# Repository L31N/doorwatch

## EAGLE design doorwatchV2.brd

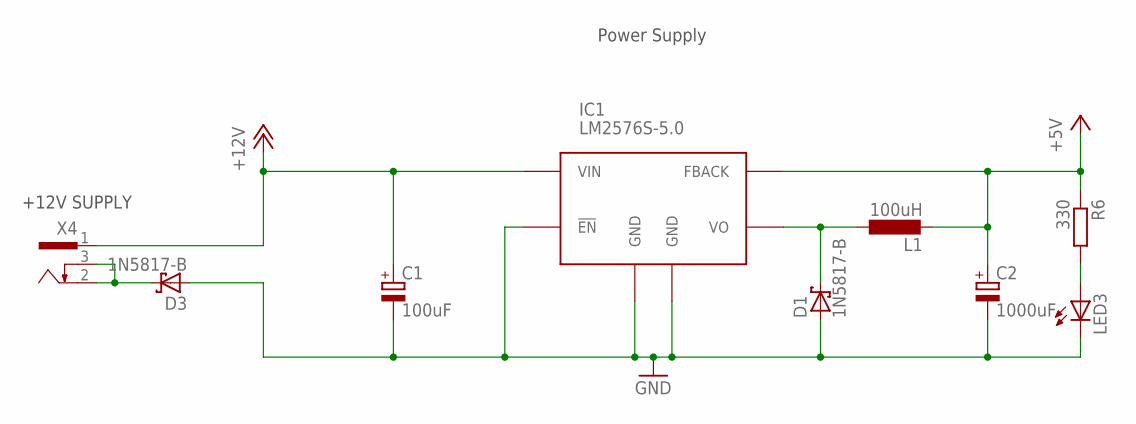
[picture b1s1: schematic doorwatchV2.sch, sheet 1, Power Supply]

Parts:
C1: 100uF; E2,5-7
C2: 1000uF; E5-10,5
D1, D3: 1N5817-B; DO41-7.6
IC1: LM2576S-5.0; TO263-5
L1: 100uH; 2200-20.32
LED3: LEDCHIP-LED0805; CHIP-LED0805
R6: 330; M0805
X4: 733980-62

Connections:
+5V: C2.+, IC1.4 (FBACK), L1.2, R6.1; also elsewhere on the board
+12V: C1.+, IC1.1 (VIN), X4.1; also elsewhere on the board
GND: C1.-, C2.-, D1.A, D3.A, IC1.3 (GND), IC1.5 (!EN), IC1.TAB (GND), LED3.C; also elsewhere on the board
unnamed: D1.C, IC1.2 (VO), L1.1
unnamed: D3.C, X4.2, X4.3
unnamed: LED3.A, R6.2

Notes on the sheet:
+12V SUPPLY
Power Supply

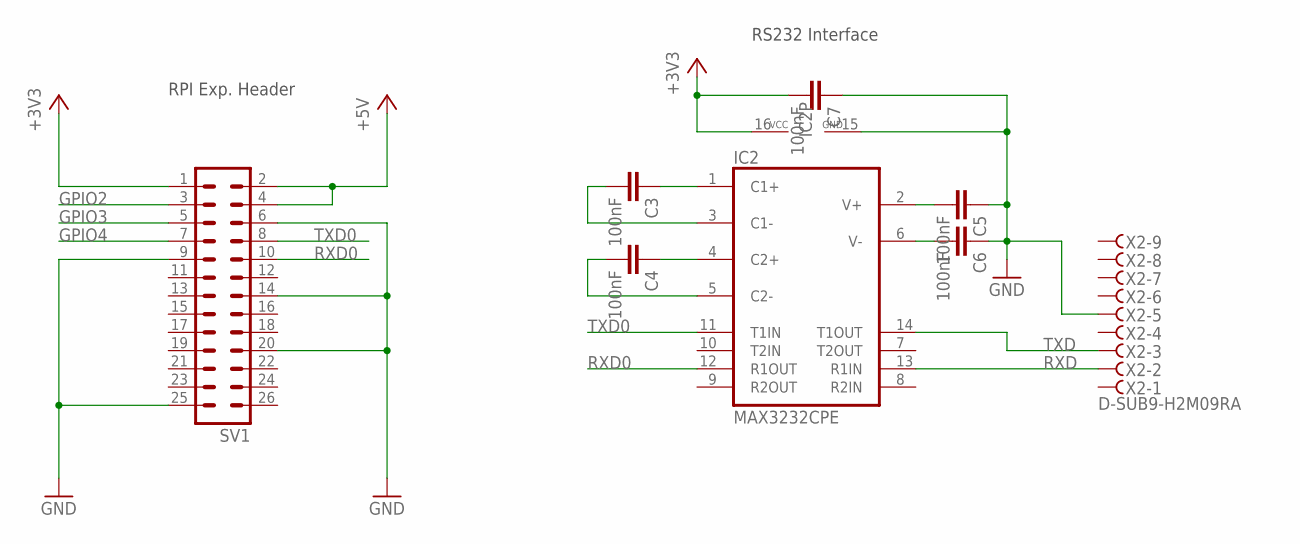
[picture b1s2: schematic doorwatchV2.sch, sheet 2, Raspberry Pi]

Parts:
C3, C4, C5, C6, C7: 100nF; C0805
IC2: MAX3232CPE; DIL16
SV1: ML26
X2: D-SUB9-H2M09RA; H2M09RA

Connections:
+3V3: C7.2, IC2.16 (VCC), SV1.1
+5V: SV1.2, SV1.4; also elsewhere on the board
GND: C5.1, C6.1, C7.1, IC2.15 (GND), SV1.6, SV1.9, SV1.14, SV1.20, SV1.25, X2.5; also elsewhere on the board
GPIO2: SV1.3; also elsewhere on the board
GPIO3: SV1.5; also elsewhere on the board
GPIO4: SV1.7; also elsewhere on the board
unnamed: C3.1, IC2.1 (C1+)
unnamed: C4.1, IC2.4 (C2+)
unnamed: C3.2, IC2.3 (C1-)
unnamed: C4.2, IC2.5 (C2-)
unnamed: C6.2, IC2.6 (V-)
unnamed: C5.2, IC2.2 (V+)
RXD: IC2.13 (R1IN), X2.2
RXD0: IC2.12 (R1OUT), SV1.10
TXD: IC2.14 (T1OUT), X2.3
TXD0: IC2.11 (T1IN), SV1.8

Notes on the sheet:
RPI Exp. Header
RS232 Interface

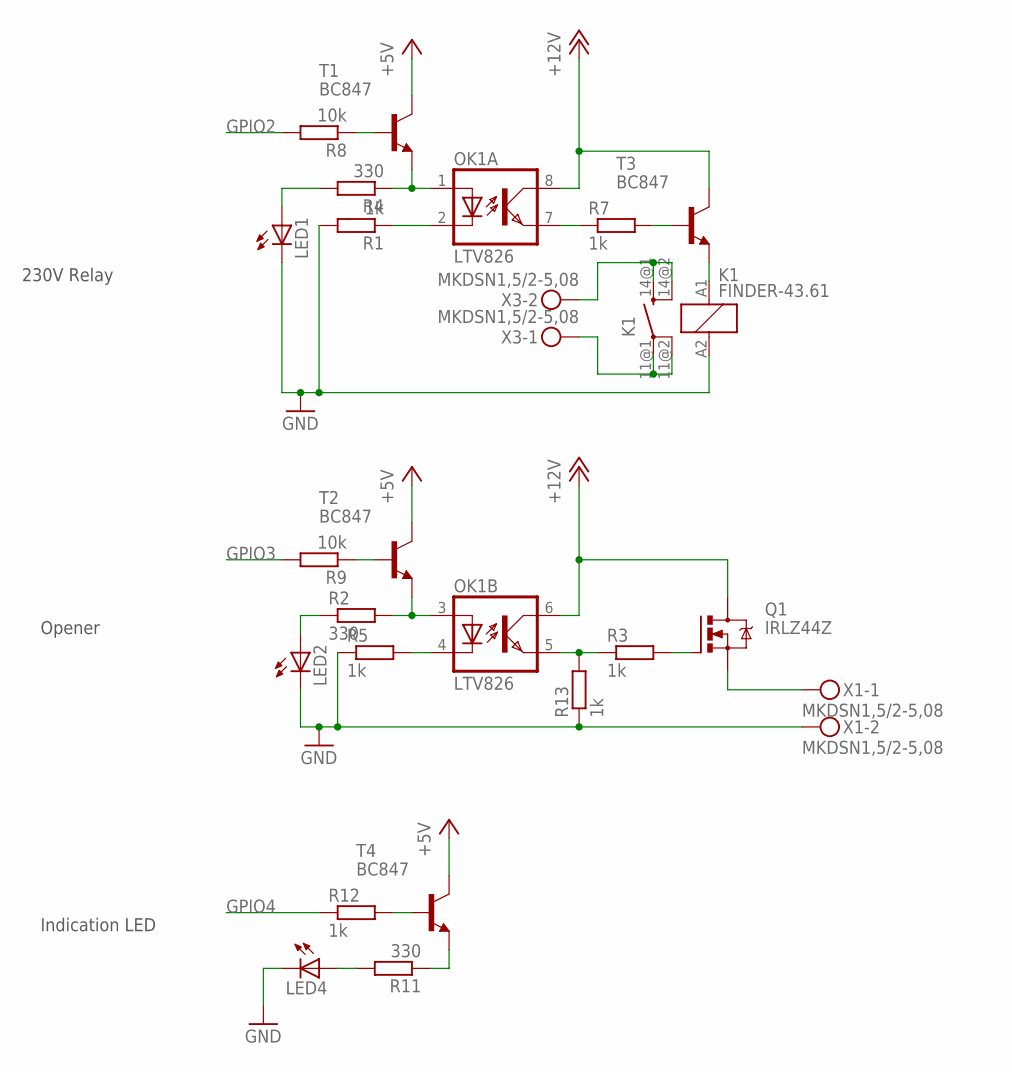
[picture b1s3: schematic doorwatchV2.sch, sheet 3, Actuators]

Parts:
K1: FINDER-43.61
LED1, LED2, LED4: LEDCHIP-LED0805; CHIP-LED0805
OK1: LTV826; DIL08
Q1: IRLZ44Z; TO220BH
R1, R3, R5, R7, R12, R13: 1k; M0805
R2, R4, R11: 330; M0805
R8, R9: 10k; M0805
T1, T2, T3, T4: BC847; SOT23
X1, X3: MKDSN1,5/2-5,08

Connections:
+5V: T1.3 (C), T2.3 (C), T4.3 (C); also elsewhere on the board
+12V: OK1.6 (COL), OK1.8 (COL), Q1.D, T3.3 (C); also elsewhere on the board
GND: K1.A2 (2), LED1.C, LED2.C, LED4.C, R1.2, R5.1, R13.1, X1.2; also elsewhere on the board
GPIO2: R8.2; also elsewhere on the board
GPIO3: R9.2; also elsewhere on the board
GPIO4: R12.1; also elsewhere on the board
unnamed: OK1.3 (A), R2.2, T2.2 (E)
unnamed: LED2.A, R2.1
unnamed: OK1.1 (A), R4.1, T1.2 (E)
unnamed: OK1.4 (C), R5.2
unnamed: LED1.A, R4.2
unnamed: Q1.S, X1.1
unnamed: OK1.2 (C), R1.1
unnamed: OK1.5 (EMIT), R3.1, R13.2
unnamed: Q1.G, R3.2
unnamed: R9.1, T2.1 (B)
unnamed: OK1.7 (EMIT), R7.1
unnamed: R7.2, T3.1 (B)
unnamed: K1.11@1 (PA), K1.11@2 (PB), X3.1
unnamed: K1.14@1 (SA), K1.14@2 (SB), X3.2
unnamed: R8.1, T1.1 (B)
unnamed: K1.A1 (1), T3.2 (E)
unnamed: R12.2, T4.1 (B)
unnamed: R11.1, T4.2 (E)
unnamed: LED4.A, R11.2

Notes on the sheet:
230V Relay
Opener
Indication LED

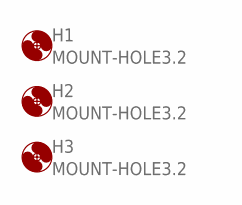
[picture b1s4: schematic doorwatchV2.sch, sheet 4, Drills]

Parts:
H1, H2, H3: MOUNT-HOLE3.2; 3,2

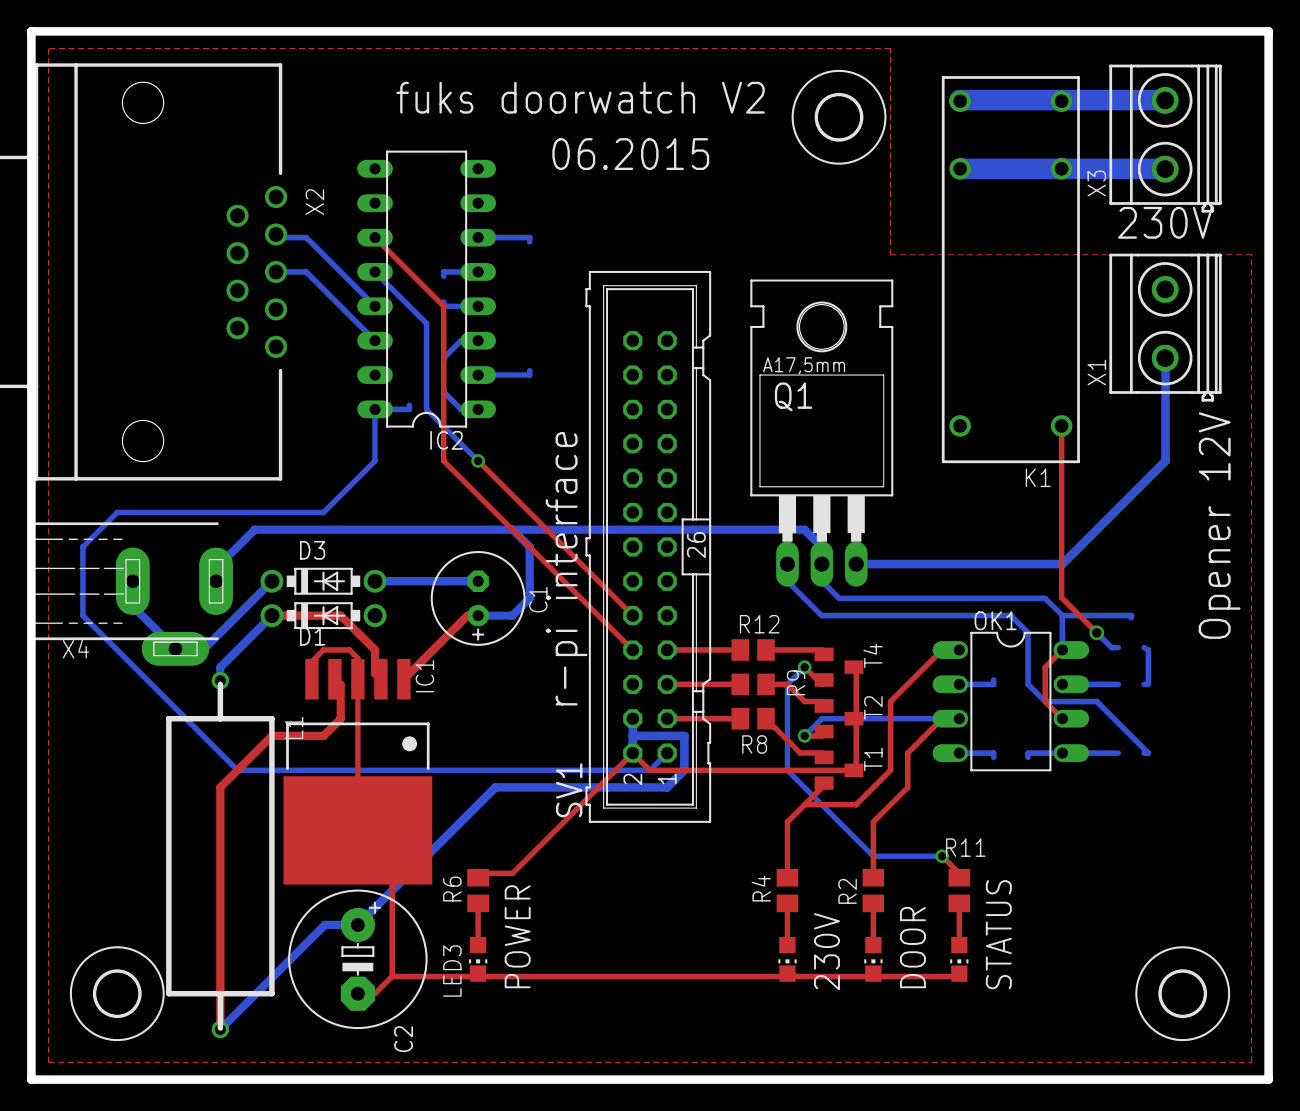
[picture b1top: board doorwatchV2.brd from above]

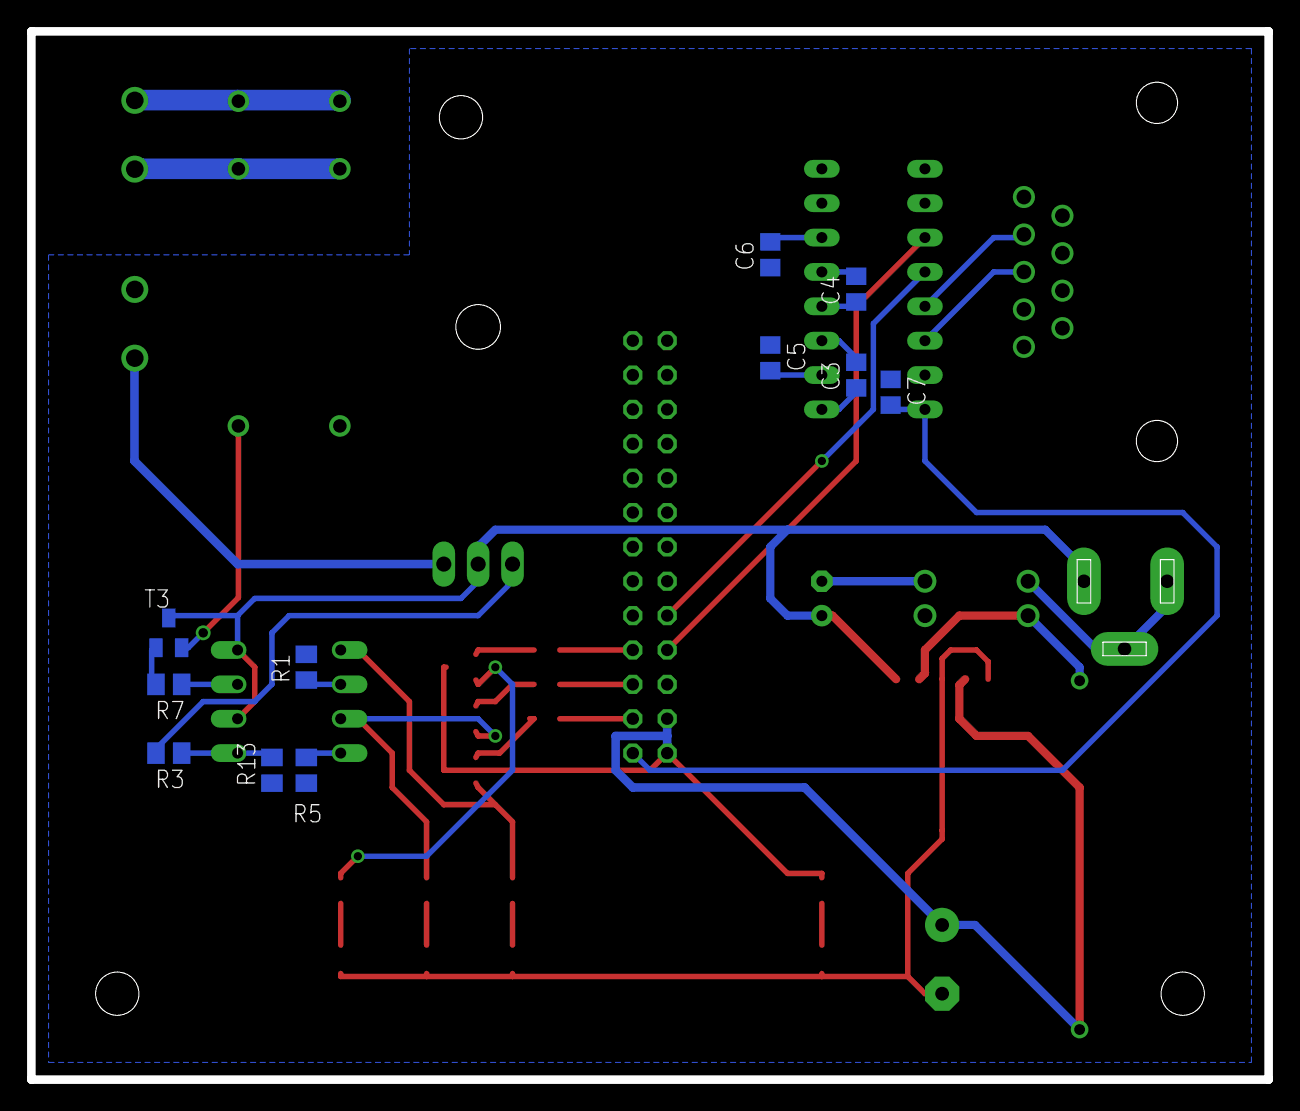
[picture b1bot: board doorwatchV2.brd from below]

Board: 2 copper layers, 91.4 x 77.5 mm, 43 parts (11 on the bottom side), 39 nets.

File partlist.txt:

Partlist

Exported from doorwatchV2.sch at 7/16/2015 1:21:18 PM

EAGLE Version 6.0.0 Copyright (c) 1988-2011 CadSoft

Assembly variant: 

Part     Value           Device          Package         Library          Sheet

C1       100uF           CPOL-EUE2.5-7   E2,5-7          rcl              1
C2       1000uF          CPOL-EUE5-10.5  E5-10,5         rcl              1
C3       100nF           C-EUC0805       C0805           rcl              2
C4       100nF           C-EUC0805       C0805           rcl              2
C5       100nF           C-EUC0805       C0805           rcl              2
C6       100nF           C-EUC0805       C0805           rcl              2
C7       100nF           C-EUC0805       C0805           rcl              2
D1       1N5817-B        1N5817-B        DO41-7.6        diode            1
D3       1N5817-B        1N5817-B        DO41-7.6        diode            1
IC1      LM2576S-5.0     LM2576S         TO263-5         regulators       1
IC2      MAX3232CPE      MAX3232CPE      DIL16           maxim            2
K1       FINDER-43.61    FINDER-43.61    FINDER-43.61    relay            3
L1       100uH           L-EU2200-20.32  2200-20.32      rcl              1
LED1                     LEDCHIP-LED0805 CHIP-LED0805    led              3
LED2                     LEDCHIP-LED0805 CHIP-LED0805    led              3
LED3                     LEDCHIP-LED0805 CHIP-LED0805    led              1
LED4                     LEDCHIP-LED0805 CHIP-LED0805    led              3
OK1      LTV826          LTV826          DIL08           optocoupler      3
Q1       IRLZ44Z         IRLZ44Z         TO220BH         transistor-power 3
R1       1k              R-EU_M0805      M0805           rcl              3
R2       330             R-EU_M0805      M0805           rcl              3
R3       1k              R-EU_M0805      M0805           rcl              3
R4       330             R-EU_M0805      M0805           rcl              3
R5       1k              R-EU_M0805      M0805           rcl              3
R6       330             R-EU_M0805      M0805           rcl              1
R7       1k              R-EU_M0805      M0805           rcl              3
R8       10k             R-EU_M0805      M0805           rcl              3
R9       10k             R-EU_M0805      M0805           rcl              3
R11      330             R-EU_M0805      M0805           rcl              3
R12      1k              R-EU_M0805      M0805           rcl              3
R13      1k              R-EU_M0805      M0805           rcl              3
SV1                      ML26            ML26            con-harting-ml   2
T1       BC847           BC847           SOT23           transistor       3
T2       BC847           BC847           SOT23           transistor       3
T3       BC847           BC847           SOT23           transistor       3
T4       BC847           BC847           SOT23           transistor       3
X1       MKDSN1,5/2-5,08 MKDSN1,5/2-5,08 MKDSN1,5/2-5,08 con-phoenix-508  3
X2       D-SUB9-H2M09RA  D-SUB9-H2M09RA  H2M09RA         con-thomas-betts 2
X3       MKDSN1,5/2-5,08 MKDSN1,5/2-5,08 MKDSN1,5/2-5,08 con-phoenix-508  3
X4                       733980-62       733980-62       con-conrad       1

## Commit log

2015-05-26 changed the power plug from USB to print connector (con-conrad)
2015-05-26 added description to eagle project
2015-05-26 adapted the optocoupler parts to 12V supply on output.
2015-05-26 added power indication LED
2015-05-27 added the 230V relay circuit
2015-05-27 fixed bug in relay circuit
2015-05-27 changed the base resistors of the transistors to 10k
2015-05-27 added GPIO indication LED
2015-05-28 splitted schematic parts to several sheets, updated descriptions, added info text. created board file (.brd)
2015-05-28 first rough layout of components
2015-05-28 added mounting-holes to schematic
2015-05-28 first version of finished layout added white-print layers and adjusted it. adapted the trace width of higher current traces
2015-05-28 fixed some DRC errors
2015-06-02 added some text components to board to sign connectors
2015-06-03 attemp to push to github
2015-06-12 created updated pdf files of schematic and board
2015-06-12 added ordering preview as pdf file and created partlist
2015-06-12 changed C1 condensator to an elko type
2015-06-12 added reichelt.de warenkorb, package of inductive has been replaced, new routing of inductive and elko are necessary
2015-06-15 merge
2015-06-15 updated board
2015-06-17 updated topplace date on board
2015-07-14 fixed two bugs: 1) wrong polarity of power-jack 2) missing pull-down resistor on output of LTV826 opto-coupler, in front of MOSFET IRLZ44Z
2015-07-14 updated changes in layout
2015-07-14 created new pdf files of schematic and board
2015-07-14 updated the package of the inductor and updated the layout
2015-07-16 removed resistor in relai circuit -> voltage was to low
2015-07-16 updated pdf files
2015-07-16 added documentation, updated some docu files
2015-07-16 removed ground around 230V part
